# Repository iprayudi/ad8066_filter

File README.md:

# ad8066_filter
 Filter board using AD8066 chip

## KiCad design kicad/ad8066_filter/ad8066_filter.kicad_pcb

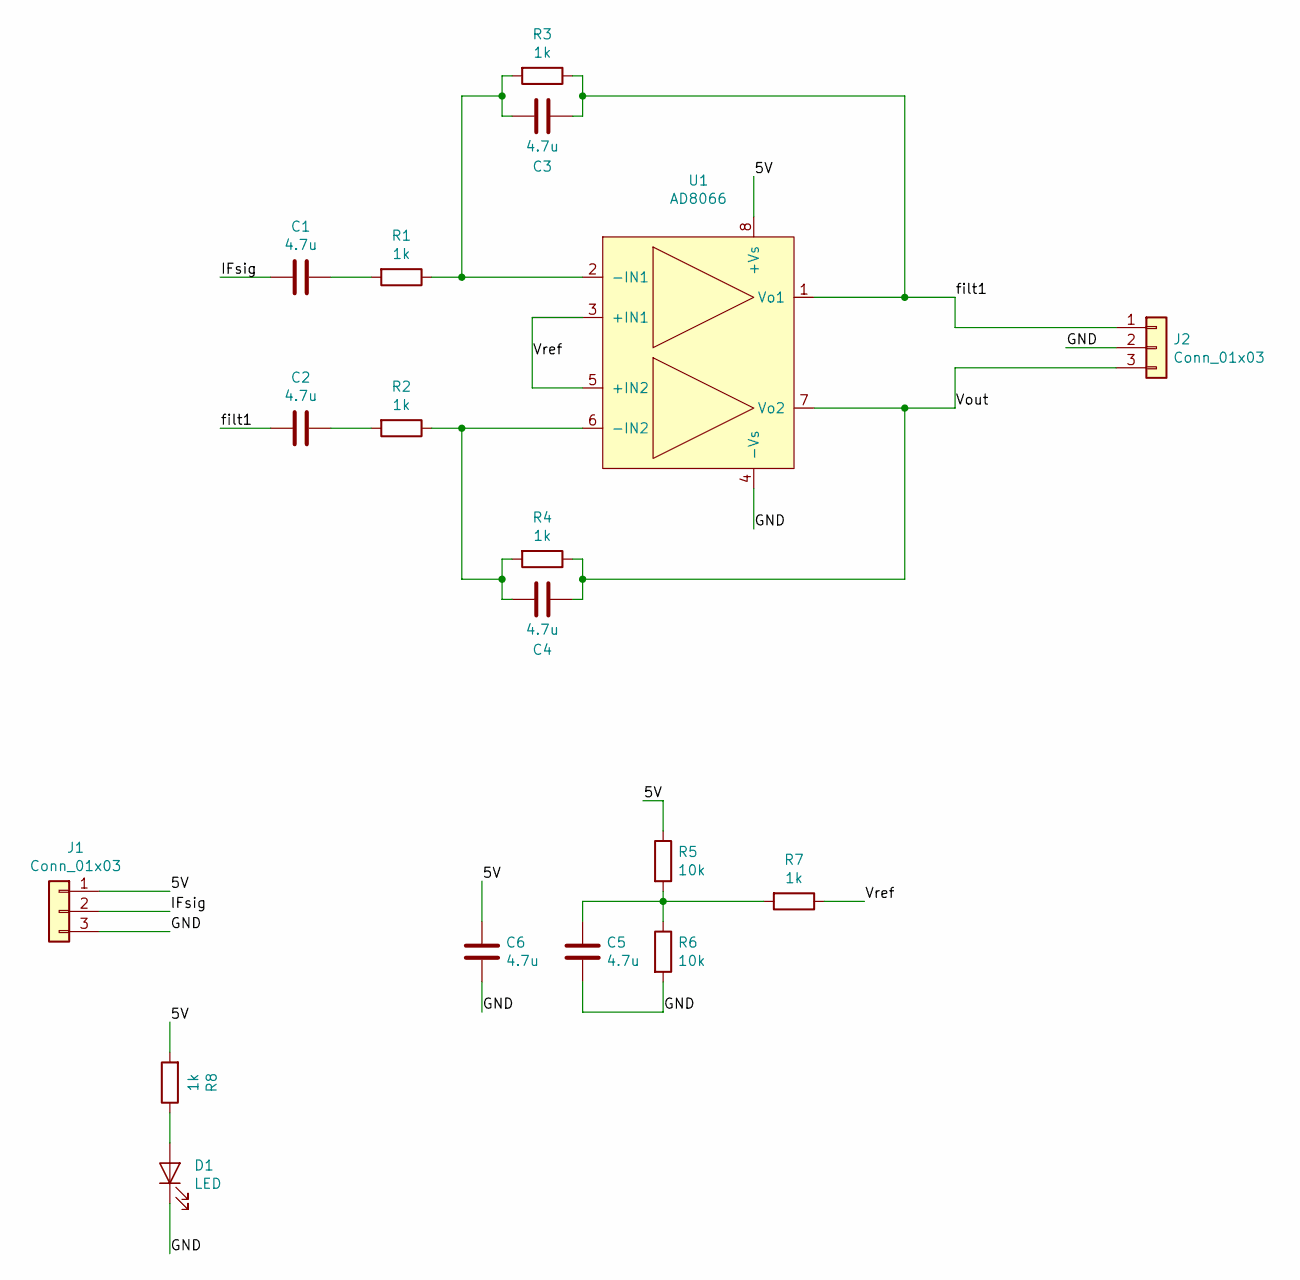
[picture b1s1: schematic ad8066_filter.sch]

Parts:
C1, C2, C3, C4, C5, C6: 4.7u; C_0805_2012Metric_Pad1.15x1.40mm_HandSolder
D1: LED; LED_0805_2012Metric_Pad1.15x1.40mm_HandSolder; LCSC C2296
J1, J2: Conn_01x03; PinHeader_1x03_P2.54mm_Vertical
R1, R2, R3, R4, R7, R8: 1k; R_0805_2012Metric_Pad1.15x1.40mm_HandSolder; LCSC C17379
R5, R6: 10k; R_0805_2012Metric_Pad1.15x1.40mm_HandSolder; LCSC C17414
U1: AD8066; SOIC-8_5.275x5.275mm_P1.27mm; LCSC C9647

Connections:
/5V: C6.1, J1.1, R5.1, R8.2, U1.8 (+Vs)
/GND: C5.2, C6.2, D1.1 (K), J1.3, J2.2, R6.2, U1.4 (-Vs)
/IFsig: C1.2, J1.2
/Vout: C4.1, J2.3, R4.1, U1.7 (Vo2)
/Vref: R7.1, U1.3 (+IN1), U1.5 (+IN2)
/filt1: C2.2, C3.1, J2.1, R3.1, U1.1 (Vo1)
unnamed: C1.1, R1.2
unnamed: C2.1, R2.2
unnamed: C3.2, R1.1, R3.2, U1.2 (-IN1)
unnamed: C4.2, R2.1, R4.2, U1.6 (-IN2)
unnamed: C5.1, R5.2, R6.1, R7.2
unnamed: D1.2 (A), R8.1

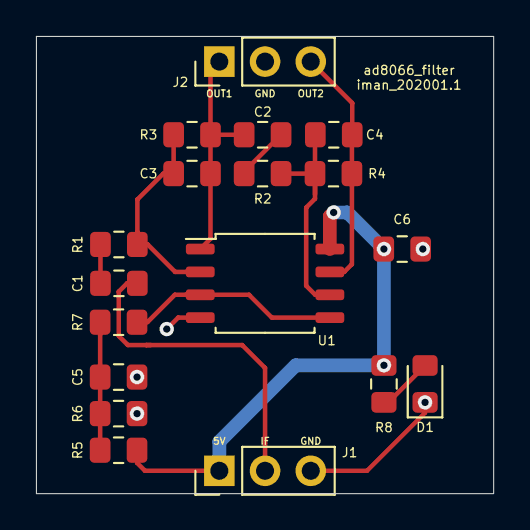
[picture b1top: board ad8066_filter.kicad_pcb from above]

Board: 2 copper layers, 25.4 x 25.4 mm, 18 parts (0 on the bottom side), 12 nets.

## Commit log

2019-12-31 schematic updated
2020-01-16 updated ltspice
